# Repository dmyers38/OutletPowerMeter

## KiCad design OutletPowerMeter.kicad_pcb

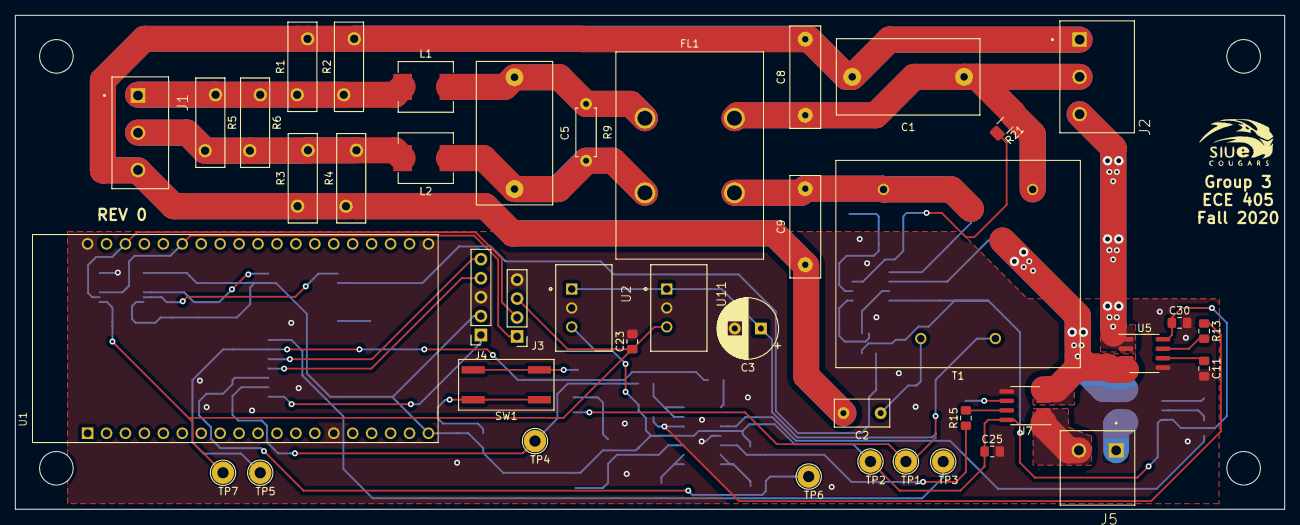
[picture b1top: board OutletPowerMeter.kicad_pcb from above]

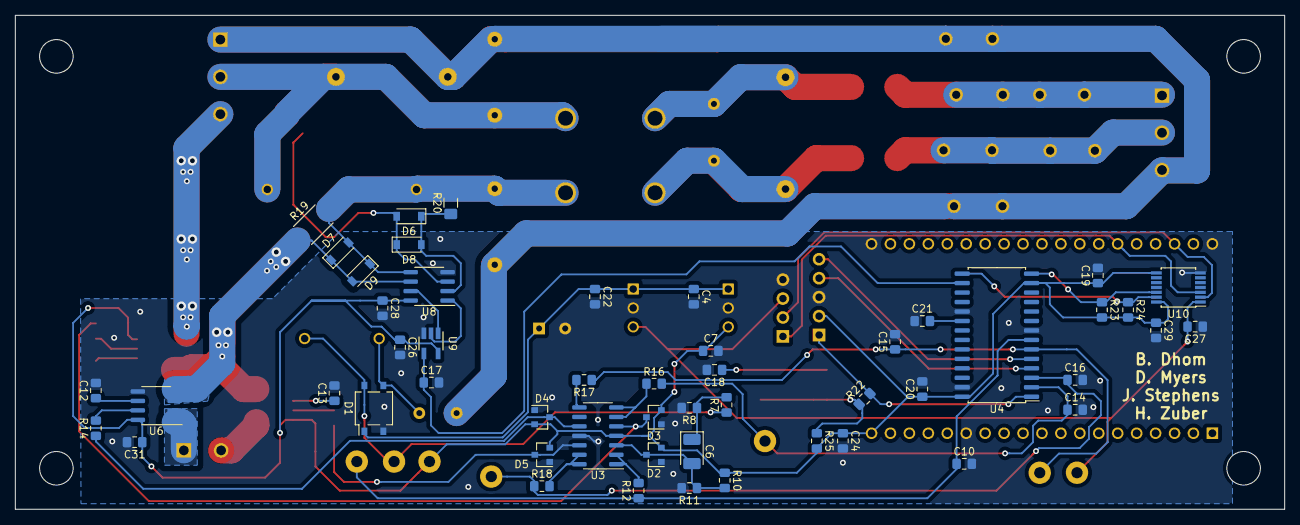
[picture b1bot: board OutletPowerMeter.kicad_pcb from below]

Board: 2 copper layers, 170.2 x 66.2 mm, 93 parts (51 on the bottom side), 51 nets.

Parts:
C1, C5: 100nF/250V; C_Rect_L19.0mm_W10.0mm_P15.00mm_MKS4
C2: 6.8nF/275V; C_Rect_L7.2mm_W3.5mm_P5.00mm_FKS2_FKP2_MKS2_MKP2
C3: 470u; CP_Radial_D8.0mm_P3.50mm
C4, C22: 10uF/50V; C_0805_2012Metric_Pad1.15x1.40mm_HandSolder
C6: 100u; CP_EIA-3528-21_Kemet-B_Pad1.50x2.35mm_HandSolder
C7, C23: 22uF/10V; C_0805_2012Metric_Pad1.15x1.40mm_HandSolder
C8, C9: 2.2nF/250V; C_Rect_L13.5mm_W3.9mm_P10.20mm_FKS3_FKP3_MKS4
C10, C14, C15, C16: 100n; C_0805_2012Metric_Pad1.15x1.40mm_HandSolder
C11, C12, C13: 1n; C_0805_2012Metric_Pad1.15x1.40mm_HandSolder
C17: 47p; C_0805_2012Metric_Pad1.15x1.40mm_HandSolder
C18, C19, C20: 0.1u; C_0805_2012Metric_Pad1.15x1.40mm_HandSolder
C21: 10u; C_0805_2012Metric_Pad1.15x1.40mm_HandSolder
C24, C25, C26, C27, C28, C29, C30, C31: 0.1uF; C_0805_2012Metric_Pad1.15x1.40mm_HandSolder
D1: MB1S; TO-269AA
D2, D3, D4, D5: BAT54S; SOT-23
D6, D7, D8, D9: 1N4148; D_SOD-123
FL1: S14100038; L_CommonMode_Wuerth_WE-CMB-L
J1: TB002-500-03BE; CUI_TB002-500-03BE
J2: TB002V-500-03BE; CUI_TB002V-500-03BK
J3: OLED; PinHeader_1x04_P2.54mm_Vertical
J4: Programmer; PinSocket_1x05_P2.54mm_Vertical
J5: TB002V-500-02BE; CUI_TB002V-500-02BE
L1, L2: MGV0603R33M-10; L_7.3x6.7_H3.0
R1, R2, R3, R4, R5, R6: MOV-10D201KTR; RV_Disc_D12mm_W3.9mm_P7.5mm_1.1mm
R7: 5.1k; R_0805_2012Metric_Pad1.15x1.40mm_HandSolder
R8: 1k; R_0805_2012Metric_Pad1.15x1.40mm_HandSolder
R9: 470k/1W; R_Axial_DIN0207_L6.3mm_D2.5mm_P7.62mm_Horizontal
R10, R11, R13, R14, R15: 10k; R_0805_2012Metric_Pad1.15x1.40mm_HandSolder
R12, R16, R17, R18: 2k; R_0805_2012Metric_Pad1.15x1.40mm_HandSolder
R19: 0.01R/5W; R_2512_6332Metric_Pad1.52x3.35mm_HandSolder
R20, R21: 1M; R_1206_3216Metric_Pad1.42x1.75mm_HandSolder
R22: 470; R_0805_2012Metric_Pad1.15x1.40mm_HandSolder
R23, R24: 2.2k; R_0805_2012Metric_Pad1.15x1.40mm_HandSolder
R25: 7.5k; R_0805_2012Metric_Pad1.15x1.40mm_HandSolder
SW1: KSC441GDCT70SHLFS; KSC4
T1: 115V / 9V; Transformer_BV301S09020-ZU
TP1, TP2, TP3, TP4, TP5, TP6, TP7: TestPoint; TestPoint_Loop_D2.54mm_Drill1.5mm_Beaded
U1: ESP32-DEVKITC-32D; MODULE_ESP32-DEVKITC-32D
U2: VX7805-500; VX78012-500_VX7805-500
U3: TLC2274; SOIC-14_3.9x8.7mm_P1.27mm
U4: dsPIC33EV32GM002; SOIC-28W_7.5x17.9mm_P1.27mm
U5, U6, U7: ACS712ELCTR-20A-T; SOIC-8_3.9x4.9mm_P1.27mm
U8: MCP6542T-I_SN; SOIC-8_3.9x4.9mm_P1.27mm
U9: SN74LVC1G86DBVR; SOT-23-5_HandSoldering
U10: ADG3304BRUZ-REEL7; TSSOP-14_4.4x5mm_P0.65mm
U11: VX7803-500; VX78012-500_VX7805-500

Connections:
3V3: C23.1, C27.2, J3.3, TP7.1, U10.1, U11.3
9V: D1.3, R7.1, T1.7, TP1.1
CURR_1: C14.1, R16.1, TP4.1, U4.2
CURR_2: C15.1, R17.1, TP5.1, U4.6
CURR_3: C16.1, R18.1, TP6.1, U4.3
EARTH: C1.2, C2.2, C8.2, C9.1, J1.3, J2.1, R1.1, R2.1, R3.2, R4.2
GND: C3.2, C4.2, C7.2, C10.2, C11.2, C12.2, C13.2, C14.2, C15.2, C16.2, C17.2, C18.2, C19.2, C20.2, C21.1, C22.2, C23.2, C24.2, C25.2, C26.2, C27.1, C28.2, C29.2, C30.2, C31.2, D1.2, D2.1, D3.1, D4.1, D5.1, J3.4, J4.3, R8.2, R11.2, U1.14, U1.20, U1.38, U2.2, U3.11, U4.8, U4.19, U4.27, U5.5, U6.5, U7.5, U8.4, U9.3, U10.7, U11.2
HOT: J1.1, L1.1, R1.2, R2.2, R5.2, R6.2
HOT_OUT: C1.1, C8.1, FL1.4, J2.2, R21.1, T1.5
I2C_SCL: R24.1, U4.15, U10.13
I2C_SCL_3V3: J3.2, U1.22, U10.2
I2C_SDA: R23.1, U4.14, U10.12
I2C_SDA_3V3: J3.1, U1.25, U10.3
MCLR: J4.1, R22.1, U4.1
NEUTRAL: J1.2, L2.2, R3.1, R4.1, R5.1, R6.1
NEUTRAL_OUT: D7.1, D9.2, R19.1, U5.3, U5.4, U6.3, U6.4, U7.3, U7.4, U8.6
NEUTRAL_SURGE: C9.2, D7.2, D9.1, FL1.3, R19.2, R20.2, T1.1, U8.5
NEUT_1: J2.3, U5.1, U5.2
NEUT_2: J5.1, U6.1, U6.2
NEUT_3: J5.2, U7.1, U7.2
unnamed: C2.1, D1.4, T1.9
unnamed: C5.1, FL1.1, L1.2, R9.2
unnamed: C5.2, FL1.2, L2.1, R9.1
unnamed: C6.1, R7.2, R8.1
unnamed: C6.2, D2.3, R10.2, R11.1, U3.3
unnamed: C11.1, U5.6
unnamed: C12.1, U6.6
unnamed: C13.1, U7.6
unnamed: C18.1, SW1.1
unnamed: C21.2, U4.20
unnamed: C3.1, C4.1, C22.1, D1.1, U2.1, U11.1
unnamed: D3.3, R13.1, U3.5
unnamed: D4.3, R14.1, U3.10
unnamed: D5.3, R15.1, U3.12
unnamed: D6.1, D8.2, R20.1, U8.2
unnamed: D6.2, D8.1, R21.2, U8.3
unnamed: R12.2, U3.1, U3.2
unnamed: R13.2, U5.7
unnamed: R14.2, U6.7
unnamed: R15.2, U7.7
unnamed: R16.2, U3.6, U3.7
unnamed: R17.2, U3.8, U3.9
unnamed: R18.2, U3.13, U3.14
unnamed: R22.2, R25.1, SW1.2
unnamed: U8.1, U9.2
unnamed: U8.7, U9.1
PF_OUT: C17.1, U4.16, U9.4
PGC: J4.5, U4.5
PGD: J4.4, U4.4
VCC: C7.1, C19.1, C20.1, C24.1, C25.1, C26.1, C28.1, C29.1, C30.1, C31.1, D2.2, D3.2, D4.2, D5.2, J4.2, R10.1, R23.2, R24.2, R25.2, TP2.1, U1.19, U2.3, U3.4, U4.13, U4.28, U5.8, U6.8, U7.8, U8.8, U9.5, U10.8, U10.14
V_SENSOR: C10.1, R12.1, TP3.1, U4.7

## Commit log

2020-09-12 Added KiCad Files
2020-09-20 Via stitched, added Vcc caps, updated mounting holes, extended the board length, etc
2020-09-20 Updated tactile switch and various footprints like current sensors and caps
2020-09-20 Added tactile switch model. Resized ground planes and more via stitching
2020-09-21 Fixed Vcc capacitors. Added more vias.
2020-09-23 Changed capacitor footprint to 1210 as well as the symbol.
2020-10-25 Revision 1 completed. Order sent to JLCPCB. Routed traces, rearranged components, and changed footprints.
    new file: Gerber.zip
    modified: OutletPowerMeter.kicad_pcb
    modified: OutletPowerMeter.kicad_pcb-bak
    modified: OutletPowerMeter.net
    modified: OutletPowerMeter.sch
    modified: OutletPowerMeter.sch-bak
2020-12-06 Updated schematic to make it more 'linear' and added the 27k resistors for power factor circuitry
2020-12-08 Attempting to fix the missing full-bridge rectifier
